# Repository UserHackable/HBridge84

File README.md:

# User Hackable HBridge84 Project

This is the User Hackable HBridge84 Project. 

It's purpose is to be a compact driver board for cars or robots. 

## Brains

The microcontroller used by this project is the ATtiny84 chip manufactured by Atmel. 
To program this chip using the [Arduino environment](https://www.arduino.cc/en/Main/Software), you will first need the [ATtiny board definition file](http://highlowtech.org/?p=1695) from [High Low Tech](http://highlowtech.org/). 

It includes:

* a C++ library for the Arduino IDE
* the Eagle Cad schematic and board layout files

# Arduino Installation

1. Start with a recent install of the [Arduino IDE](https://www.arduino.cc/en/Main/Software).
2. Install the [ATtiny library from High Low Tech](http://highlowtech.org/?p=1695).
3. Make sure you have an AVR ICSP programmer like the [Sparkfun Pocket AVR Programmer](https://www.sparkfun.com/products/9825) with it's drivers installed. 
4. Install this library by placing this entire folder as a subfolder in your Arduino/libraries folder.

## HBridge84 

### Board dimensions

* (200000, 130000) original units
* (2.0000, 1.3000) inches
* (50.8000, 33.0200) mm

| Front | Back |
| --- | --- |
|  |  |

## RJ11Breakout 

### Board dimensions

* (70000, 70000) original units
* (0.7000, 0.7000) inches
* (17.7800, 17.7800) mm

| Front | Back |
| --- | --- |
|  |  |

## RJ11-ICSP-Breakout 

### Board dimensions

* (90000, 100000) original units
* (0.9000, 1.0000) inches
* (22.8600, 25.4000) mm

| Front | Back |
| --- | --- |
|  |  |

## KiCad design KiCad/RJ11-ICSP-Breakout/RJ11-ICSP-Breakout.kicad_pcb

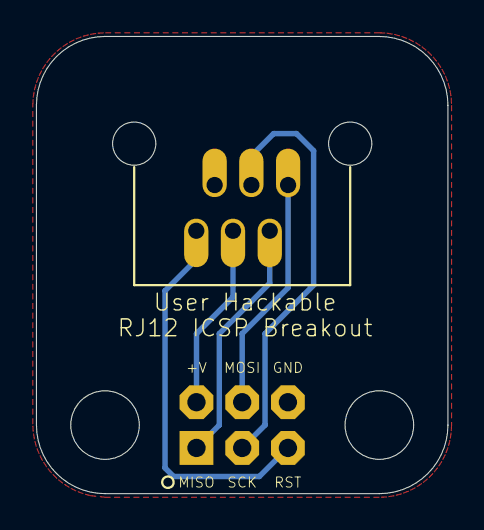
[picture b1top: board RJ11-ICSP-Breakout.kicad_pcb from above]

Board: 2 copper layers, 22.9 x 25.4 mm, 4 parts (0 on the bottom side), 6 nets.

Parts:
J5: ICSP; 2X3-NS
U$7: RJ12
UNK_HOLE_0: dummyfp0
UNK_HOLE_1: dummyfp1

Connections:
4: J5.3, U$7.4
5: J5.1, U$7.5
5V: J5.2, U$7.3
6: J5.4, U$7.6
GND: J5.6, U$7.2
RST: J5.5, U$7.1

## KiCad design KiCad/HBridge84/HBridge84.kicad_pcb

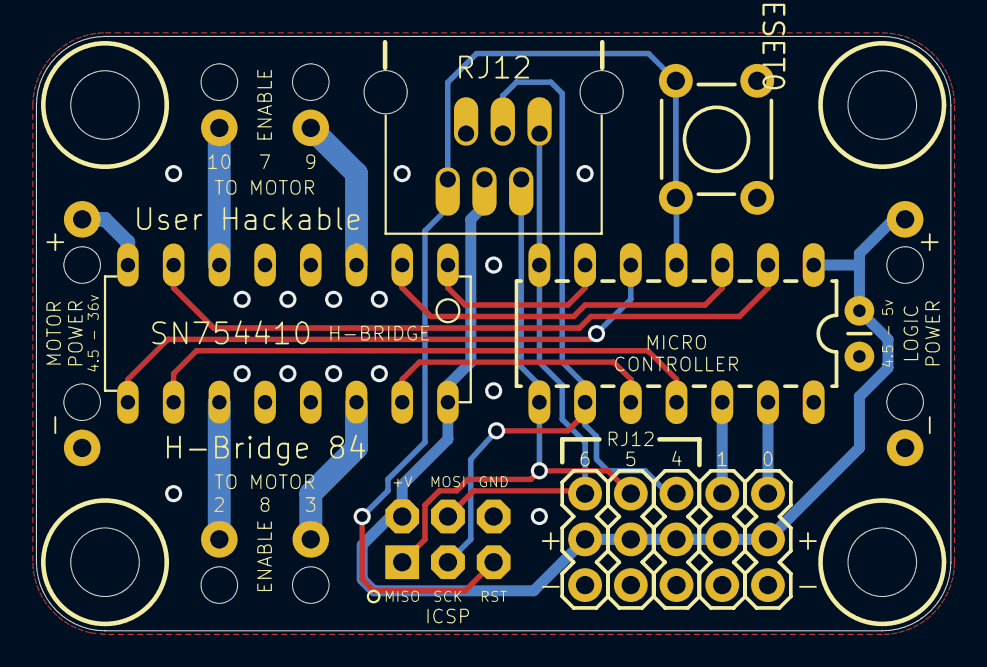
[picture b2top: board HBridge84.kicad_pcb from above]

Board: 2 copper layers, 50.8 x 33.0 mm, 23 parts (0 on the bottom side), 19 nets.

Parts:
C2: CAP-PTH-SMALL
J0, J1, J2, J3, J4: 1X03
J5: ICSP; 2X3-NS
RESET0: TACTILE-PTH
SN754410: SN754410; DIP16
U$1, U$3, U$4, U$5, U$6, U$8, U$9, U$10: M1; M1_NO_STRAIN
U$2: ATTINY84; DIL14
U$7: RJ12
UNK_HOLE_0: dummyfp0
UNK_HOLE_1: dummyfp1
UNK_HOLE_2: dummyfp2
UNK_HOLE_3: dummyfp3

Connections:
0: J0.3, U$2.13
1: J1.3, U$2.12
2: SN754410.10, U$2.11
3: SN754410.15, U$2.10
4: J2.3, J5.3, U$2.9, U$7.4
5: J3.3, J5.1, U$2.8, U$7.5
5V: C2.1, J0.2, J1.2, J2.2, J3.2, J4.2, J5.2, SN754410.16, U$2.1, U$7.3, U$10.P$1
6: J4.3, J5.4, U$2.7, U$7.6
7: SN754410.1, U$2.6
8: SN754410.9, U$2.5
9: SN754410.2, U$2.3
10: SN754410.7, U$2.2
GND: C2.2, J0.1, J1.1, J2.1, J3.1, J4.1, J5.6, RESET0.1, RESET0.2, SN754410.4, SN754410.5, SN754410.12, SN754410.13, U$2.14, U$7.2, U$8.P$1, U$9.P$1
OUT1: SN754410.3, U$1.P$1
OUT2: SN754410.6, U$3.P$1
OUT3: SN754410.11, U$4.P$1
OUT4: SN754410.14, U$5.P$1
RST: J5.5, RESET0.3, RESET0.4, U$2.4, U$7.1
V_BATT: SN754410.8, U$6.P$1

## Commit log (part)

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2016-03-11 first_commit
2016-03-11 updating readme
2016-03-11 updating examples
2016-03-11 adding eagle files
2016-03-11 changing backward to reverse
2016-03-11 all examples work
2016-03-12 updating pcb image
2016-03-12 give examples meaningful names
2016-03-26 adding in md files
2016-03-26 updating readme.md
2016-03-26 foobar
2016-03-26 updating ICSP breakout
2016-03-26 updating README.rb
2016-03-26 fleeble
2016-03-26 update ICSP breakout
2016-03-26 adding in gerber zip files
2016-03-26 fixing ICSP breakout border
2016-04-06 updating
2016-04-07 from Makefile
2016-04-22 added bare basic
2016-05-06 Uploaded line follower
2016-05-06 added linefollower
